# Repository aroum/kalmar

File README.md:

# Kalmar

My [Architeuthis dux](https://github.com/tapioki/cephalopoda/tree/main/Architeuthis%20dux) keyboard modification.

## Differences:
* Power switch
* Reset button
* Solder jumper for ProMicro(no need to flip the controller)
* Low profile case with magnets
* Additional mounting holes for case

# BOM for keyboard

| Item                                                                   | Quantity | Remarks                              |
| ---------------------------------------------------------------------- | -------: | ------------------------------------ |
| [proMicro](https://aliexpress.ru/item/32840365436.html)                | 2        | or any other compatible controller   |
| [Kailh Choc V1](https://aliexpress.ru/item/32959996455.html)           | 34       | switches                             |
| [Keycaps](https://aliexpress.ru/item/33026798318.html)                 | 34       | 1U                                   |
| [Magnets](https://aliexpress.ru/item/1005002757445161.html)            | 2-6      | disc 7x2 mm (for case)               |
| [Bumpers](https://aliexpress.ru/item/4001188580018.html)               | 18       | 5x2 mm (for case)                   |
| [Sockets PH3.5](https://aliexpress.ru/item/32899635835.html)           | 12x2     | for controller                       |
| [SMD button 3x4x2mm](https://aliexpress.ru/item/1005003812819985.html) | 2        | for reset                            |
| [MSK-12C02](https://aliexpress.ru/item/1005001398386692.html)          | 2        | Power switch  (wireless only)        |
| [301230](https://aliexpress.ru/item/32732458079.html)                  | 2        | Battery  (wireless only)             |

Interactive BOM is located ```/pcb/ibom/ibom.html```

# GERBER

GERBER can be downloaded in [releases](https://github.com/aroum/kalmar/releases).

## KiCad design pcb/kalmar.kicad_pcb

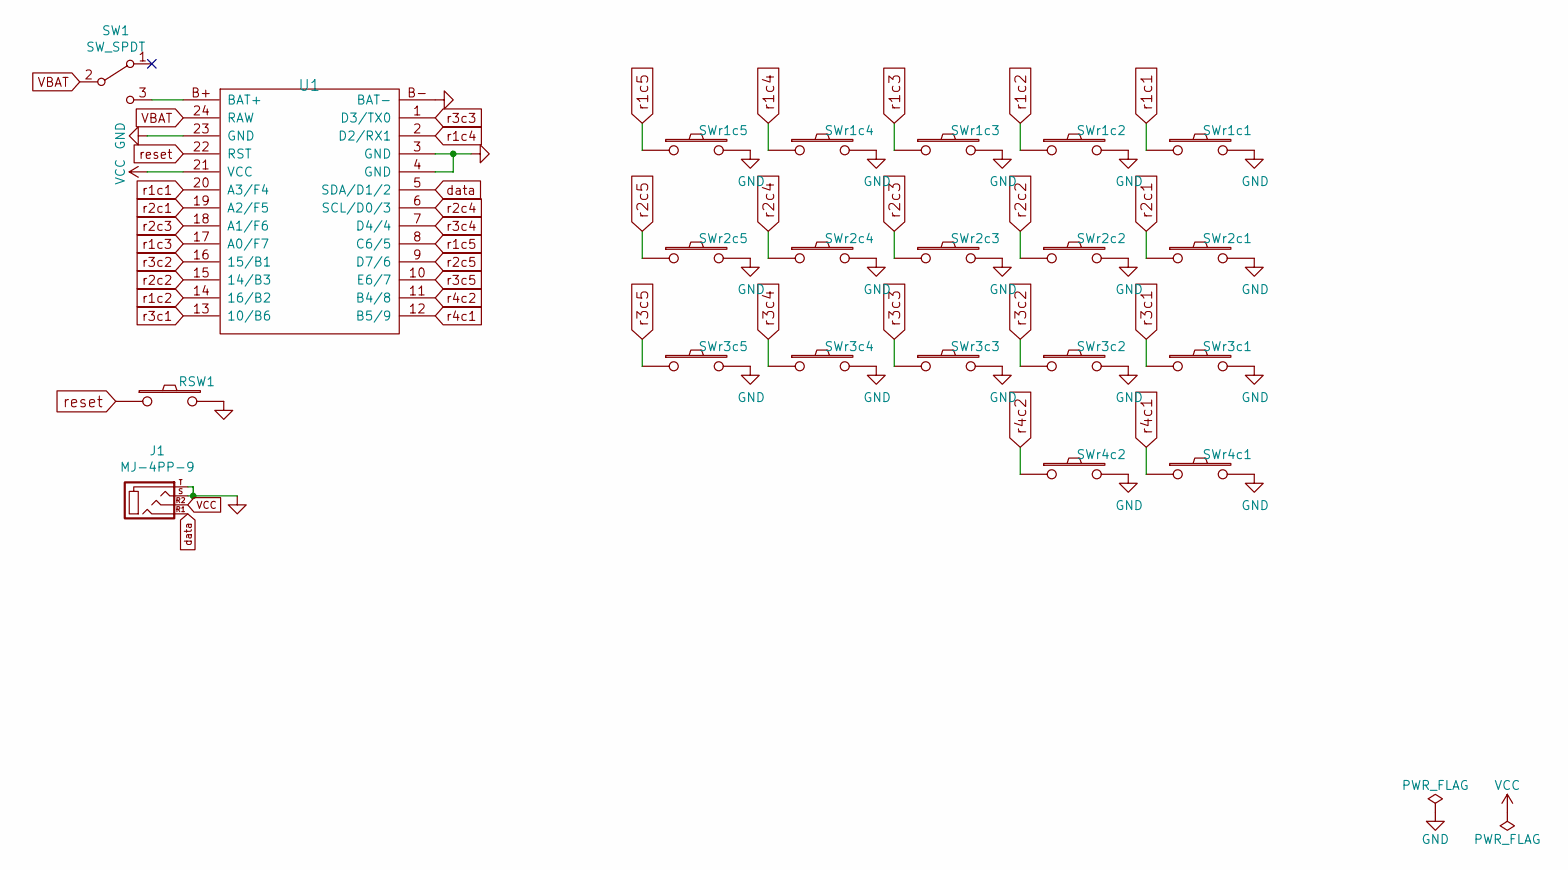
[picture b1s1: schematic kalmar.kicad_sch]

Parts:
J1: MJ-4PP-9; MJ-4PP-9_dual
RSW1: SW_PUSH; SW_3x4x2_2legs_x2
SW1: SW_SPDT; switch_MSK-12C02_smd_x2
SWr1c1, SWr1c2, SWr1c3, SWr1c4, SWr1c5, SWr2c1, SWr2c2, SWr2c3, SWr2c4, SWr2c5, SWr3c1, SWr3c2, SWr3c3, SWr3c4, SWr3c5, SWr4c1, SWr4c2: SW_PUSH; ChocV1_duplex_hotswap
U1: ProMicro_r; ProMicro_duplex_clean

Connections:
GND: J1.S, J1.T, RSW1.2, SWr1c1.2, SWr1c2.2, SWr1c3.2, SWr1c4.2, SWr1c5.2, SWr2c1.2, SWr2c2.2, SWr2c3.2, SWr2c4.2, SWr2c5.2, SWr3c1.2, SWr3c2.2, SWr3c3.2, SWr3c4.2, SWr3c5.2, SWr4c1.2, SWr4c2.2, U1.3 (GND), U1.4 (GND), U1.23 (GND), U1.B- (BAT-)
unnamed: SW1.3 (C), U1.B+ (BAT+)
VBAT: SW1.2 (B), U1.24 (RAW)
VCC: J1.R2, U1.21 (VCC)
data: J1.R1, U1.5 (SDA/D1/2)
r1c1: SWr1c1.1, U1.20 (A3/F4)
r1c2: SWr1c2.1, U1.14 (16/B2)
r1c3: SWr1c3.1, U1.17 (A0/F7)
r1c4: SWr1c4.1, U1.2 (D2/RX1)
r1c5: SWr1c5.1, U1.8 (C6/5)
r2c1: SWr2c1.1, U1.19 (A2/F5)
r2c2: SWr2c2.1, U1.15 (14/B3)
r2c3: SWr2c3.1, U1.18 (A1/F6)
r2c4: SWr2c4.1, U1.6 (SCL/D0/3)
r2c5: SWr2c5.1, U1.9 (D7/6)
r3c1: SWr3c1.1, U1.13 (10/B6)
r3c2: SWr3c2.1, U1.16 (15/B1)
r3c3: SWr3c3.1, U1.1 (D3/TX0)
r3c4: SWr3c4.1, U1.7 (D4/4)
r3c5: SWr3c5.1, U1.10 (E6/7)
r4c1: SWr4c1.1, U1.12 (B5/9)
r4c2: SWr4c2.1, U1.11 (B4/8)
reset: RSW1.1, U1.22 (RST)

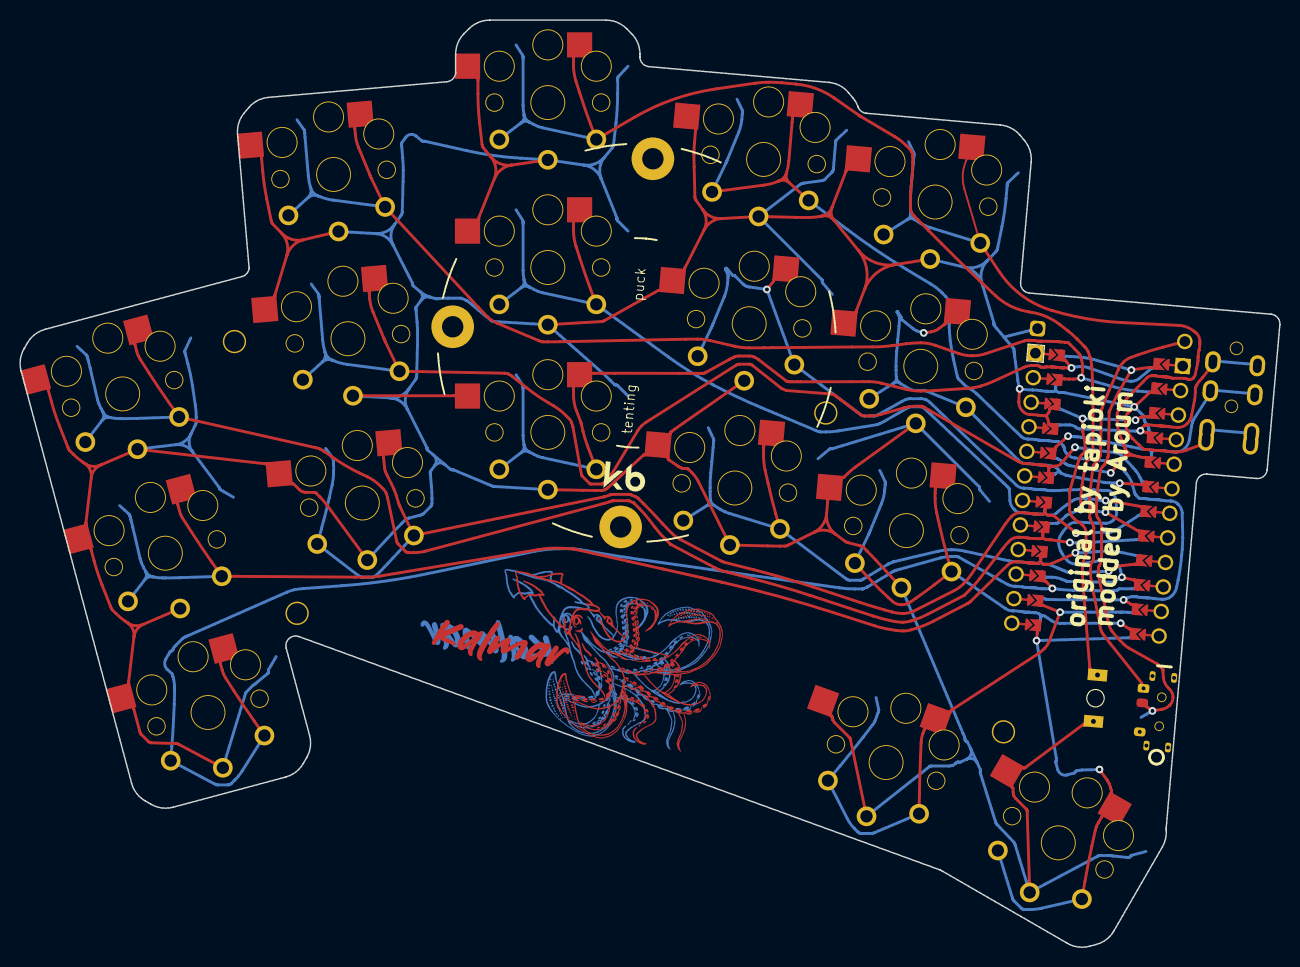
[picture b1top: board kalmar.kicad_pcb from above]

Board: 2 copper layers, 129.9 x 95.6 mm, 25 parts (1 on the bottom side), 23 nets.

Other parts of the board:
H1, H2, H3, H5: Hole; HOLE

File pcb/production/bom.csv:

Designator,Footprint,Quantity,Value,LCSC Part #
"H1, H2, H3, H5",HOLE,4,Hole,
J1,MJ-4PP-9_dual,1,MJ-4PP-9,
RSW1,SW_3x4x2_2legs_x2,1,SW_PUSH,
SW1,switch_MSK-12C02_smd_x2,1,SW_SPDT,
"SWr1c1, SWr1c2, SWr1c3, SWr1c4, SWr1c5, SWr2c1, SWr2c2, SWr2c3, SWr2c4, SWr2c5, SWr3c1, SWr3c2, SWr3c3, SWr3c4, SWr3c5, SWr4c1, SWr4c2",ChocV1_duplex_hotswap_topor,17,SW_PUSH,
U,ProMicro_duplex_clean,1,ProMicro_r,

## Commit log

2022-09-18 init
2023-09-30 some fixes
2024-02-07 v0.3
    fix connection
    add jack cut
